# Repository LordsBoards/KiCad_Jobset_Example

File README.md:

# An KiCad 9 jobset example, based on an STM32U585 Pro Micro

To use this jobset template, copy it to your project directory and click "File > Open Jobset File..."

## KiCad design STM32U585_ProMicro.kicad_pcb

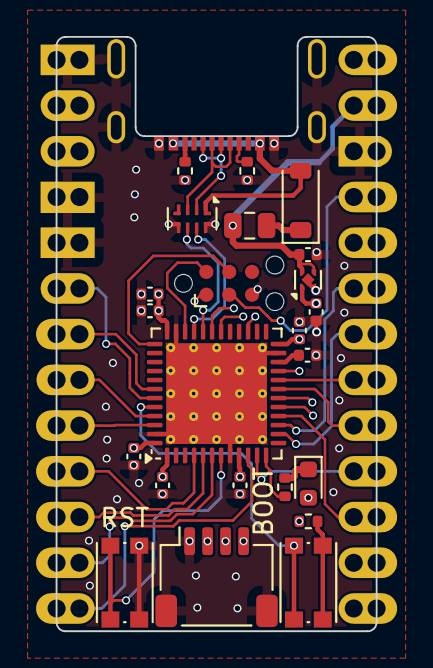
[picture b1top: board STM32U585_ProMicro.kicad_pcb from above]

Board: 8 copper layers, 17.8 x 33.0 mm, 25 parts (0 on the bottom side), 39 nets.

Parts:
C1, C2: 1uF; C_0402_1005Metric
C3, C4, C5, C6, C8: 100nF; C_0402_1005Metric
C7: 4.7uF; C_0402_1005Metric
C9: 10uF; C_0402_1005Metric
D1: LED_Small; LED_0603_1608Metric
D2: D_Small; D_SOD-123
F1: Polyfuse_Small; Fuse_0805_2012Metric
J1: Conn_ARM_SWD_TagConnect_TC2030-NL; Tag-Connect_TC2030-IDC-NL_2x03_P1.27mm_Vertical
J2: Conn_01x04_MountingPin; JST_SH_SM04B-SRSS-TB_1x04-1MP_P1.00mm_Horizontal
J3: USB_C_Receptacle_USB2.0_16P; USB_C_Receptacle_Jing_918-418K2024S40000
J102: Conn_02x13_Top_Bottom; Connector_Pro_Micro_Castellated
R1, R2, R4: 5.1kR; R_0402_1005Metric
R3: 220R; R_0402_1005Metric
SW1, SW2: SW_Push; SW_Push_1P1T_NO_CK_KMR2
U1: STM32U585CIUx; QFN-48-1EP_7x7mm_P0.5mm_EP5.6x5.6mm_ThermalVias
U2: NCP115AMX250TCG; OnSemi_XDFN4-1EP_1.0x1.0mm_EP0.52x0.52mm
U4: ECMF02-4CMX8; ST_UQFN-8L_1.2x2.5mm_P0.5mm

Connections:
+3.3V: C2.1, C3.1, C4.1, C5.1, C6.1, C8.1, C9.1, D1.2 (A), J1.1 (VCC), J2.2, J102.18, R4.1, U1.1 (VBAT), U1.9 (VDDA), U1.24 (VDD), U1.36 (VDD), U1.48 (VDD), U2.1 (OUT)
/BOOT0: SW1.1, U1.44 (PH3)
/D0/RX: J102.3, U1.31 (USART1_RX)
/D1/TX: J102.2, U1.30 (USART1_TX)
/D2/SDA: J102.6, U1.43 (I2C1_SDA)
/D3/SCL: J102.7, U1.42 (I2C1_SCL)
/D4/CAN_RX: J102.8, U1.45 (FDCAN1_RX)
/D5/CAN_TX: J102.9, U1.46 (FDCAN1_TX)
/D6: J102.10, U1.4 (PC15)
/D7: J102.11, U1.5 (PH0)
/D8: J102.12, U1.6 (PH1)
/D9: J102.13, U1.10 (PA0)
/D10: J102.26, U1.18 (PB0)
/D14/MISO: J102.24, U1.16 (SPI1_MISO)
/D15/SCLK: J102.23, U1.11 (SPI1_SCK)
/D16/MOSI: J102.25, U1.17 (SPI1_MOSI)
/D18: J102.22, U1.19 (PB1)
/D19: J102.21, U1.20 (PB2)
/D20: J102.20, U1.14 (PA4)
/D21: J102.19, U1.15 (PA5)
/LED: R3.2, U1.12 (PA2)
/SCL_QWIIC: J2.4, U1.21 (I2C2_SCL)
/SDA_QWIIC: J2.3, U1.27 (I2C2_SDA)
/SWCLK: J1.4 (SWCLK), U1.37 (DEBUG_JTCK-SWCLK)
/SWDIO: J1.2 (SWDIO), U1.34 (DEBUG_JTMS-SWDIO)
/USB_D+: J3.A6 (D+), J3.B6 (D+), U4.2 (D-_in)
/USB_D-: J3.A7 (D-), J3.B7 (D-), U4.3 (D+_in)
/USB_DN: U1.32 (USB_OTG_FS_DM), U4.6 (D+_out)
/USB_DP: U1.33 (USB_OTG_FS_DP), U4.7 (D-_out)
/~RST: J1.3 (~RESET), J102.17, SW2.1, U1.7 (NRST)
GND: C1.2, C2.2, C3.2, C4.2, C5.2, C6.2, C7.2, C8.2, C9.2, J1.5 (GND), J2.1, J2.MP (MountPin), J3.A1 (GND), J3.S1 (SHIELD), J102.1, J102.4, J102.5, J102.16, R1.2, R2.2, SW2.2, U1.8 (VSSA), U1.23 (VSS), U1.35 (VSS), U1.47 (VSS), U1.49 (VSS), U2.2 (GND), U2.5 (GND), U4.5 (GND), U4.8 (GND)
unnamed: D1.1 (K), R3.1
unnamed: D2.2 (A), J3.A4 (VBUS), U4.1 (VBUS)
unnamed: D2.1 (K), F1.1
unnamed: J3.A5 (CC1), R1.1
unnamed: J3.B5 (CC2), R2.1
unnamed: R4.2, SW1.2
unnamed: C7.1, U1.22 (VCAP)
VBUS: C1.1, F1.2, J102.15, U2.3 (EN), U2.4 (IN)

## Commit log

2025-04-02 Initial commit.
